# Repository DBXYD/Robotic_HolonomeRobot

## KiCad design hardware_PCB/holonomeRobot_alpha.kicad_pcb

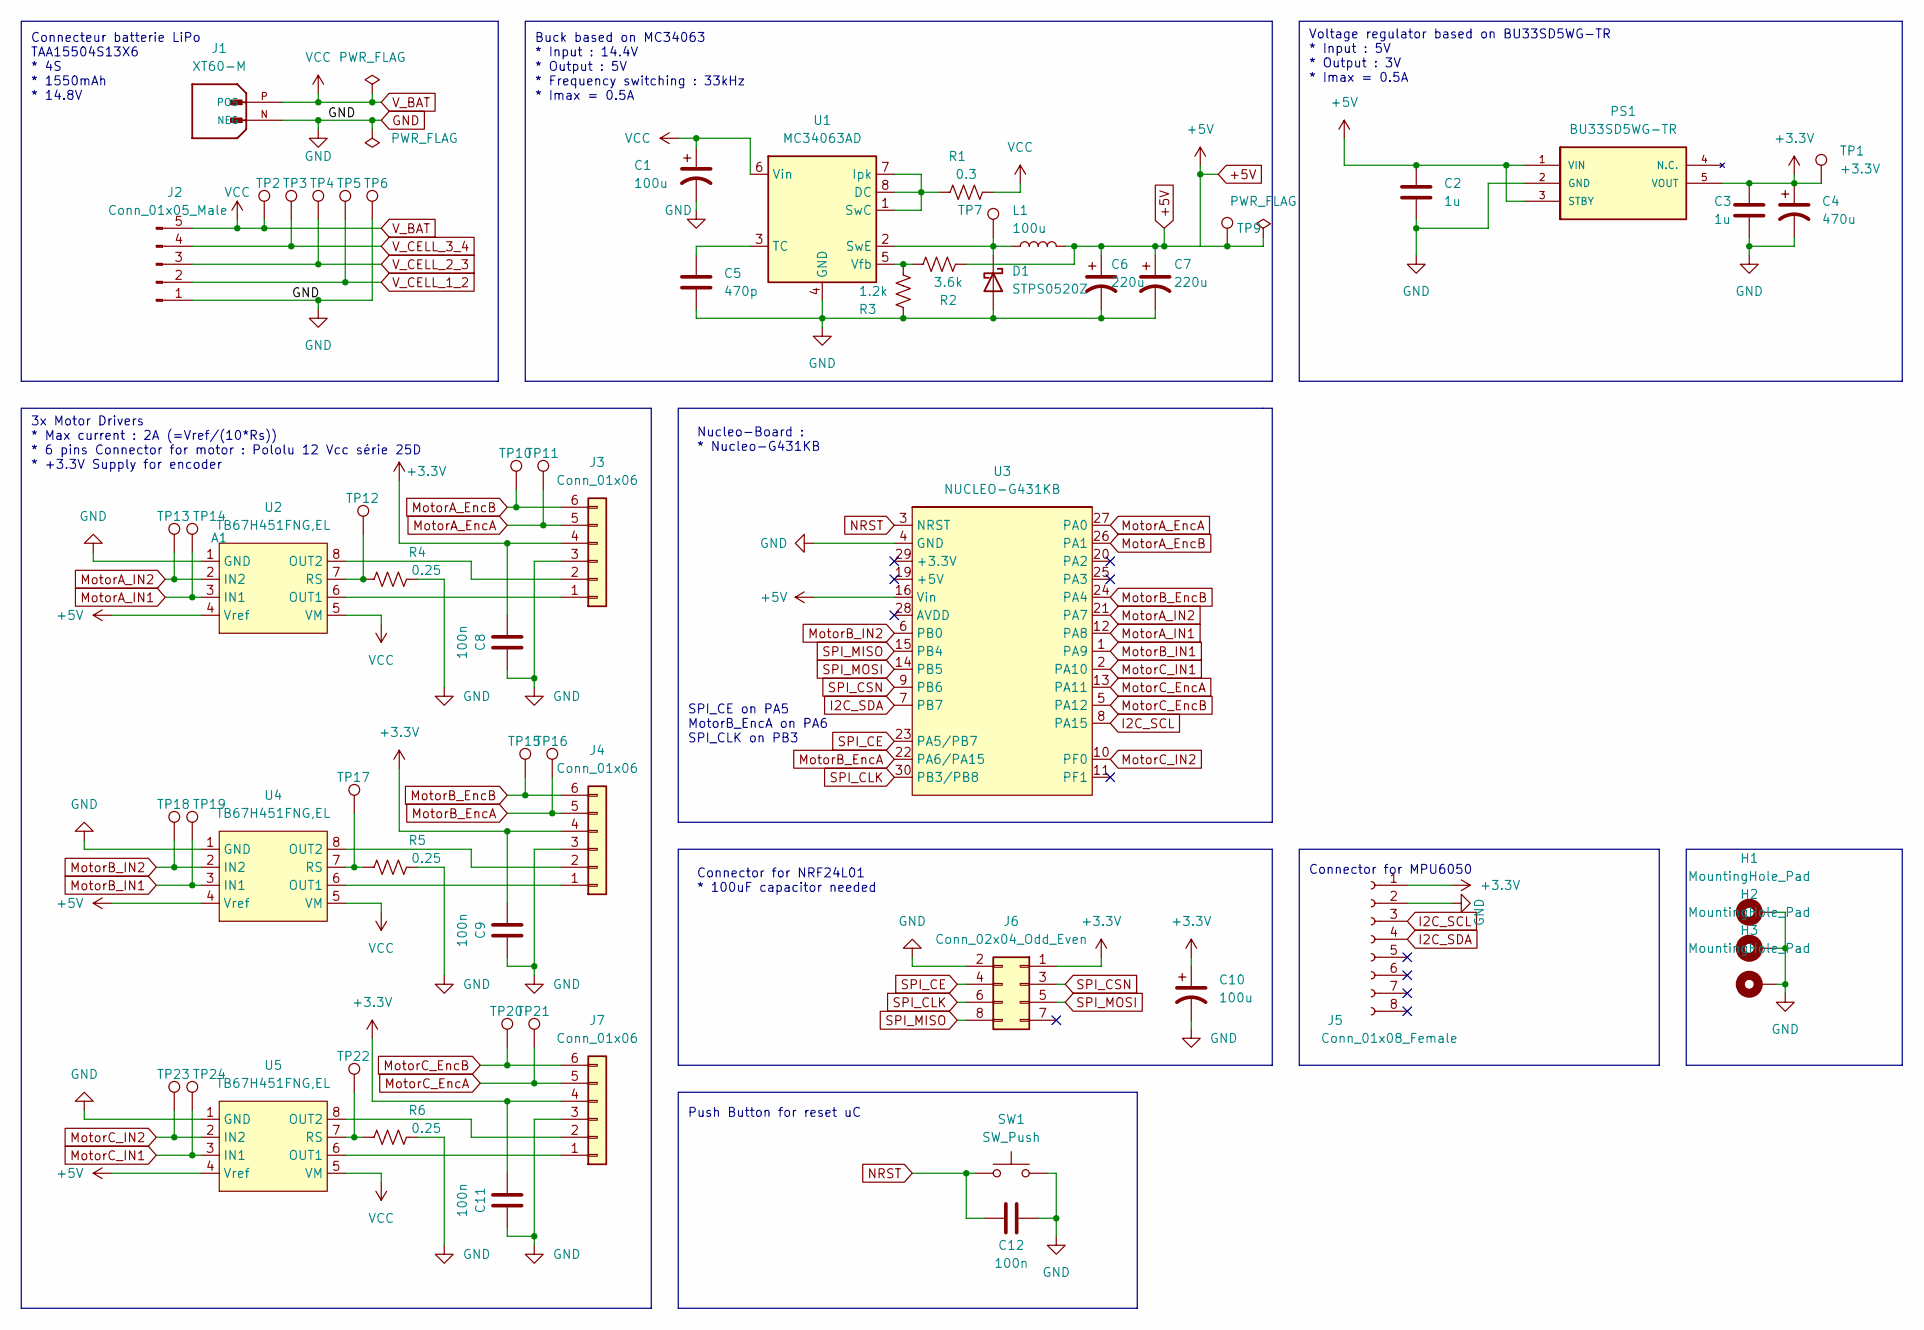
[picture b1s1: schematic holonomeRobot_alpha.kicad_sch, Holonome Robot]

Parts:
C1, C10: 100u; CP_Elec_6.3x7.7
C2, C3: 1u; C_0603_1608Metric_Pad1.08x0.95mm_HandSolder
C4: 470u; CP_Elec_10x10.5
C5: 470p; C_0603_1608Metric_Pad1.08x0.95mm_HandSolder
C6, C7: 220u; CP_Elec_8x10.5
C8, C9, C11, C12: 100n; C_0603_1608Metric_Pad1.08x0.95mm_HandSolder
D1: STPS0520Z; D_SOD-123
H1, H2, H3: MountingHole_Pad; MountingHole_3.2mm_M3_Pad
J1: XT60-M; AMASS_XT60-M; PARTREV V1.2
J2: Conn_01x05_Male; JST_XH_B5B-XH-A_1x05_P2.50mm_Vertical
J3, J4, J7: Conn_01x06; JST_XH_S6B-XH-A_1x06_P2.50mm_Horizontal
J5: Conn_01x08_Female; PinSocket_1x08_P2.54mm_Vertical
J6: Conn_02x04_Odd_Even; PinSocket_2x04_P2.54mm_Vertical
L1: 100u; L_12x12mm_H6mm
PS1: BU33SD5WG-TR; SOT95P280X125-5N; Manufacturer_Part_Number BU33SD5WG-TR; Mouser_Part_Number 755-BU33SD5WG-TR
R1: 0.3; R_0603_1608Metric_Pad0.98x0.95mm_HandSolder
R2: 3.6k; R_0603_1608Metric_Pad0.98x0.95mm_HandSolder
R3: 1.2k; R_0603_1608Metric_Pad0.98x0.95mm_HandSolder
R4, R5, R6: 0.25; R_0603_1608Metric_Pad0.98x0.95mm_HandSolder
SW1: SW_Push; SW_SMD_2-1437565-8_4_4.50_6.00_6.00_5.00
TP1: +3.3V; TestPoint_Pad_D1.0mm
TP2: V_BAT; TestPoint_Pad_D1.0mm
TP3: V_CELL_3_4; TestPoint_Pad_D1.0mm
TP4: V_CELL_2_3; TestPoint_Pad_D1.0mm
TP5: V_CELL_1_2; TestPoint_Pad_D1.0mm
TP6: GND_BAT; TestPoint_Pad_D1.0mm
TP7: BUCK_OUT; TestPoint_Pad_D1.0mm
TP9: +5V; TestPoint_Pad_D1.0mm
TP10: AEncB; TestPoint_Pad_D1.0mm
TP11: AEncA; TestPoint_Pad_D1.0mm
TP12: RsA; TestPoint_Pad_D1.0mm
TP13: A2; TestPoint_Pad_D1.0mm
TP14: A1; TestPoint_Pad_D1.0mm
TP15: BEncB; TestPoint_Pad_D1.0mm
TP16: BEncA; TestPoint_Pad_D1.0mm
TP17: RsB; TestPoint_Pad_D1.0mm
TP18: B2; TestPoint_Pad_D1.0mm
TP19: B1; TestPoint_Pad_D1.0mm
TP20: CEncB; TestPoint_Pad_D1.0mm
TP21: CEncA; TestPoint_Pad_D1.0mm
TP22: RsC; TestPoint_Pad_D1.0mm
TP23: C2; TestPoint_Pad_D1.0mm
TP24: C1; TestPoint_Pad_D1.0mm
U1: MC34063AD; SOIC-8_3.9x4.9mm_P1.27mm
U2, U4, U5: TB67H451FNG,EL; HSOP-8-1EP_3.9x4.9mm_P1.27mm_EP2.41x3.1mm
U3: NUCLEO-G431KB; MODULE_NUCLEO-G431KB

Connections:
+3.3V: C3.1, C4.1, C8.2, C9.2, C10.1, C11.2, J3.4, J4.4, J5.1, J6.1, J7.4, PS1.5 (VOUT), TP1.1
+5V: C2.1, C6.1, C7.1, L1.2, PS1.1 (VIN), PS1.3 (STBY), R2.2, TP9.1, U2.4 (Vref), U3.16 (Vin), U4.4 (Vref), U5.4 (Vref)
GND: C1.2, C2.2, C3.2, C4.2, C5.2, C6.2, C7.2, C8.1, C9.1, C10.2, C11.1, C12.1, D1.2 (A), H1.1, H2.1, H3.1, J1.N (NEG), J2.1, J3.3, J4.3, J5.2, J6.2, J7.3, PS1.2 (GND), R3.2, R4.2, R5.2, R6.2, SW1.2, TP6.1, U1.4 (GND), U2.1 (GND), U3.4 (GND), U4.1 (GND), U5.1 (GND)
I2C_SCL: J5.3, U3.8 (PA15)
I2C_SDA: J5.4, U3.7 (PB7)
MotorA_EncA: J3.5, TP11.1, U3.27 (PA0)
MotorA_EncB: J3.6, TP10.1, U3.26 (PA1)
MotorA_IN1: TP14.1, U2.3 (IN1), U3.12 (PA8)
MotorA_IN2: TP13.1, U2.2 (IN2), U3.21 (PA7)
MotorB_EncA: J4.5, TP16.1, U3.22 (PA6/PA15)
MotorB_EncB: J4.6, TP15.1, U3.24 (PA4)
MotorB_IN1: TP19.1, U3.1 (PA9), U4.3 (IN1)
MotorB_IN2: TP18.1, U3.6 (PB0), U4.2 (IN2)
MotorC_EncA: J7.5, TP21.1, U3.13 (PA11)
MotorC_EncB: J7.6, TP20.1, U3.5 (PA12)
MotorC_IN1: TP24.1, U3.2 (PA10), U5.3 (IN1)
MotorC_IN2: TP23.1, U3.10 (PF0), U5.2 (IN2)
NRST: C12.2, SW1.1, U3.3 (NRST)
unnamed: C5.1, U1.3 (TC)
unnamed: D1.1 (K), L1.1, TP7.1, U1.2 (SwE)
unnamed: J3.1, U2.6 (OUT1)
unnamed: J3.2, U2.8 (OUT2)
unnamed: J7.1, U5.6 (OUT1)
unnamed: J7.2, U5.8 (OUT2)
unnamed: R1.1, U1.1 (SwC), U1.7 (Ipk), U1.8 (DC)
unnamed: R2.1, R3.1, U1.5 (Vfb)
unnamed: R4.1, TP12.1, U2.7 (RS)
unnamed: R5.1, TP17.1, U4.7 (RS)
unnamed: R6.1, TP22.1, U5.7 (RS)
unnamed: J4.1, U4.6 (OUT1)
unnamed: J4.2, U4.8 (OUT2)
SPI_CE: J6.4, U3.23 (PA5/PB7)
SPI_CLK: J6.6, U3.30 (PB3/PB8)
SPI_CSN: J6.3, U3.9 (PB6)
SPI_MISO: J6.8, U3.15 (PB4)
SPI_MOSI: J6.5, U3.14 (PB5)
V_BAT: C1.1, J1.P (POS), J2.5, R1.2, TP2.1, U1.6 (Vin), U2.5 (VM), U4.5 (VM), U5.5 (VM)
V_CELL_1_2: J2.2, TP5.1
V_CELL_2_3: J2.3, TP4.1
V_CELL_3_4: J2.4, TP3.1

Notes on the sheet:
3x Motor Drivers * Max current : 2A (=Vref/(10*Rs)) * 6 pins Connector for motor : Pololu 12 Vcc série 25D * +3.3V Supply for encoder
SPI_CE on PA5 MotorB_EncA on PA6 SPI_CLK on PB3
Voltage regulator based on BU33SD5WG-TR * Input : 5V * Output : 3V * Imax = 0.5A
Connector for MPU6050
Connector for NRF24L01 * 100uF capacitor needed
Push Button for reset uC
Connecteur batterie LiPo TAA15504S13X6 * 4S * 1550mAh * 14.8V
Nucleo-Board : * Nucleo-G431KB
Buck based on MC34063 * Input : 14.4V * Output : 5V * Frequency switching : 33kHz * Imax = 0.5A

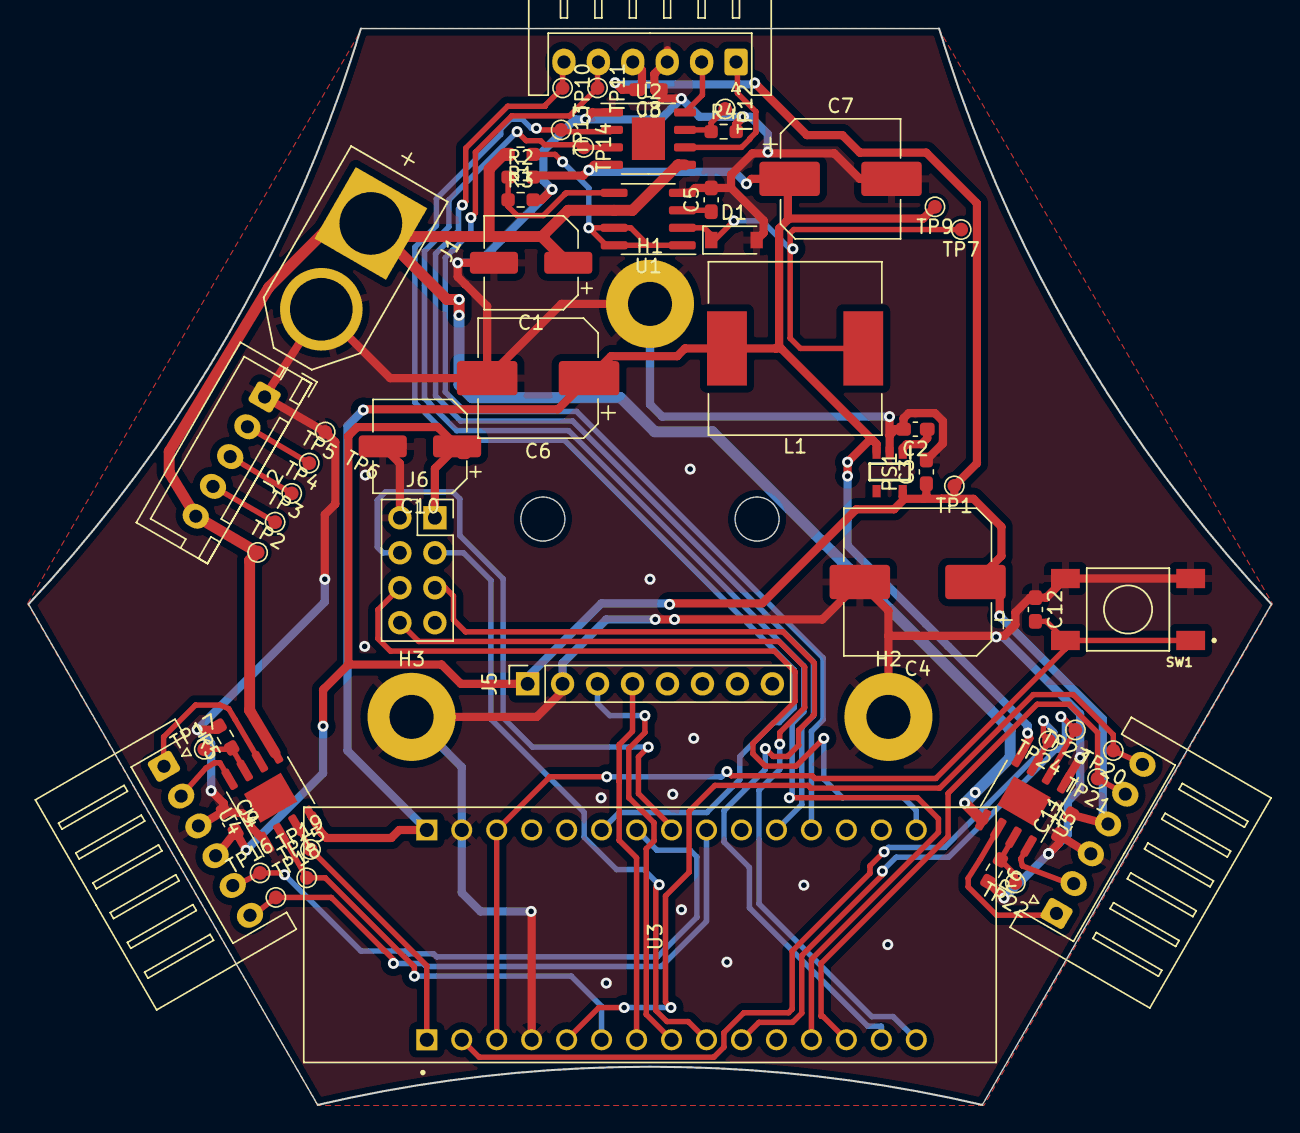
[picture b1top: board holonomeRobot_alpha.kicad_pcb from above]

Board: 2 copper layers, 90.3 x 78.2 mm, 60 parts (0 on the bottom side), 40 nets.

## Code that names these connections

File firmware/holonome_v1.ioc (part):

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Mcu.Name=STM32G431K(6-8-B)Tx
Mcu.Package=LQFP32
Mcu.UserName=STM32G431KBTx
PA0.Signal=S_TIM2_CH1
PA1.Signal=S_TIM2_CH2
PA10.Signal=S_TIM1_CH3
PA11.Signal=S_TIM4_CH1
PA12.Signal=S_TIM4_CH2
PA13.GPIOParameters=GPIO_Label
PA13.GPIO_Label=T_SWDIO
PA13.Mode=Serial_Wire
PA13.Signal=SYS_JTMS-SWDIO
PA14.GPIOParameters=GPIO_Label
PA14.GPIO_Label=T_SWCLK
PA14.Mode=Serial_Wire
PA14.Signal=SYS_JTCK-SWCLK
PA15.Mode=I2C
PA15.Signal=I2C1_SCL
PA2.GPIOParameters=GPIO_Label
PA2.GPIO_Label=USART2_TX [ST-LINKV3E_VCP_RX]
PA2.Mode=Asynchronous
PA2.Signal=USART2_TX
PA3.GPIOParameters=GPIO_Label
PA3.GPIO_Label=USART2_RX [ST-LINKV3E_VCP_TX]
PA3.Mode=Asynchronous
PA3.Signal=USART2_RX
PA4.Signal=S_TIM3_CH2
PA5.GPIOParameters=GPIO_Label
PA5.GPIO_Label=SPI1_CE
PA5.Signal=GPIO_Output
PA6.Signal=S_TIM3_CH1
PA7.Mode=PWM Generation1 CH1 CH1N
PA7.Signal=TIM1_CH1N
PA8.Signal=S_TIM1_CH1
PA9.Signal=S_TIM1_CH2
PB0.Mode=PWM Generation2 CH2 CH2N
PB0.Signal=TIM1_CH2N
PB3.Mode=Full_Duplex_Master
PB3.Signal=SPI1_SCK
PB4.Mode=Full_Duplex_Master
PB4.Signal=SPI1_MISO
PB5.Mode=Full_Duplex_Master
PB5.Signal=SPI1_MOSI
PB6.GPIOParameters=GPIO_Label
PB6.GPIO_Label=SPI1_CSN
PB6.Signal=GPIO_Output
PB7.Mode=I2C
PB7.Signal=I2C1_SDA
PB8-BOOT0.GPIOParameters=GPIO_Label
PB8-BOOT0.GPIO_Label=LED
PB8-BOOT0.Signal=GPIO_Output
PF0-OSC_IN.Mode=PWM Generation3 CH3 CH3N
PF0-OSC_IN.Signal=TIM1_CH3N
RCC.HSE_VALUE=8000000
RCC.SYSCLKFreq_VALUE=170000000
RCC.SYSCLKSource=RCC_SYSCLKSOURCE_PLLCLK
board=NUCLEO-G431KB
boardIOC=true
